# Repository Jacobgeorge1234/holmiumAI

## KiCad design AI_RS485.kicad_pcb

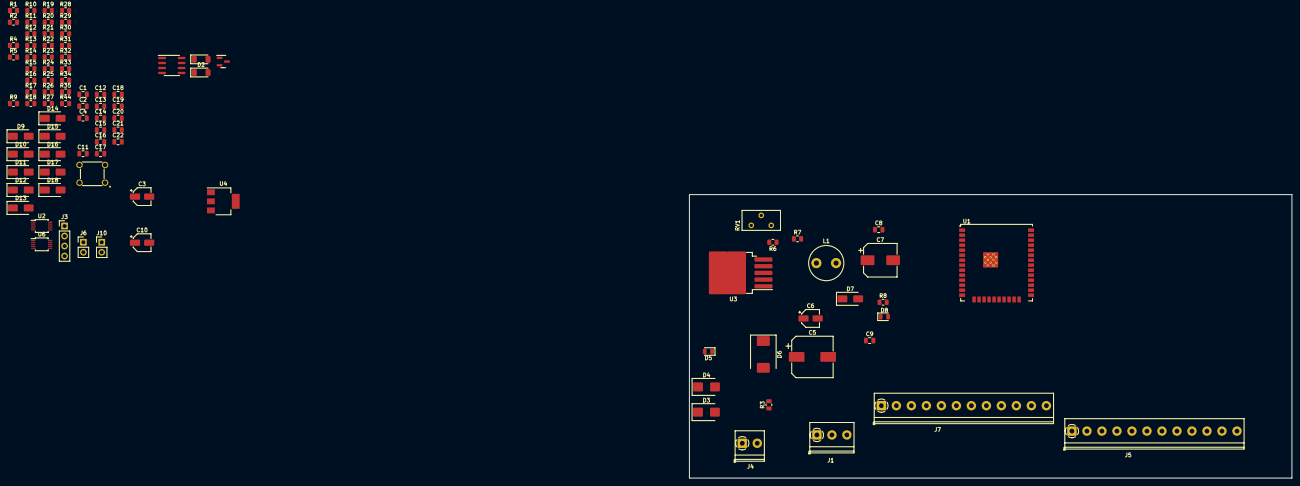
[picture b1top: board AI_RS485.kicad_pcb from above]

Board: 2 copper layers, 153.0 x 72.0 mm, 93 parts (0 on the bottom side), 55 nets, no tracks yet.

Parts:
C1: 1uF/50V; C_0805_2012Metric
C2, C12, C13, C14, C15, C16, C17, C18, C19, C20, C21, C22: 100nF/50V; C_0805_2012Metric
C3, C6, C10: 1uF; CP_Elec_4x5.4
C4, C8: 100nF; C_0805_2012Metric
C5: 100uF; CP_Elec_10x10
C7: 330uF; CP_Elec_8x10
C9, C11: 1uF; C_0805_2012Metric
D1, D2: 1N4148; D_MiniMELF
D3, D4: SMBJ36CA; D_SMB
D5, D8: LED; LED_0805_2012Metric
D6: SS54; D_SMC
D7: SS34; D_SMA
D9, D10, D11, D12, D13, D14, D15, D16, D17, D18: SMBJ6CA; D_SMA
J1: Conn_01x03; CONNECTORx3
J3: Conn_01x04_Socket; PinHeader_1x04_P2.54mm_Vertical
J4: Conn_01x02_Socket; CONNECTORx2
J5, J7: Conn_01x12_Socket; CONNECTORx12
J6: Conn_01x02_Pin; PinHeader_1x02_P2.54mm_Vertical
J10: Conn_01x02_Male; PinHeader_1x02_P2.54mm_Vertical
L1: 68uH; L_Radial_D8.7mm_P5.00mm_Fastron_07HCP
Q1: BC847; SOT-23
R1: 10k; R_0805_2012Metric
R2, R17, R18, R19, R20, R21, R22, R23: 220; R_0805_2012Metric
R3, R4, R5, R7, R8: 4K7; R_0805_2012Metric
R6, R12, R13: 1K; R_0805_2012Metric
R9, R10, R28, R29, R30, R31, R32, R33, R34, R35: 10K; R_0805_2012Metric
R11, R16, R25, R44: 0E; R_0805_2012Metric
R14, R15: 510E; R_0805_2012Metric
R24: 120E; R_0805_2012Metric
R26, R27: R; R_0805_2012Metric
RV1: 4K7; Potentiometer_Bourns_3386X_Horizontal
SW1: SW_Push; BNF_Pushbutton
U1: ESP32-WROOM-32U
U2, U6: ADS1115IDGS; TSSOP-10_3x3mm_P0.5mm
U3: LM2596S-ADJ; TO-263-5_TabPin3
U4: AMS1117-3.3; SOT-223-3_TabPin2
U5: MAX3485; SOIC-8_3.9x4.9mm_P1.27mm

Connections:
485_TX: R9.1, R12.1
+3.3V: C2.1, C3.1, C4.1, J10.1, R1.2, R10.1, R14.2, R26.1, R27.1, R28.2, R29.2, R30.2, R31.2, R32.2, R33.2, R34.2, R35.2, U1.2 (VDD), U5.8 (VCC)
+5V: C12.1, C14.1, U2.8 (VDD), U6.1 (ADDR), U6.8 (VDD)
+12V: D4.2, D5.1 (K), D6.2 (A), J4.2
ADS_DRDY_1: U1.4 (SENSOR_VP), U2.2 (ALERT/RDY)
ADS_DRDY_2: U1.5 (SENSOR_VN), U6.2 (ALERT/RDY)
AIN_0: C15.1, C19.1, R2.1, R20.1, U2.4 (AIN0)
AIN_1: C16.1, C20.1, R19.1, R23.1, U2.5 (AIN1)
AIN_2: C17.1, C21.1, R17.1, R21.1, U2.6 (AIN2)
AIN_3: C18.1, C22.1, R18.1, R22.1, U2.7 (AIN3)
BOOT: J6.1, U1.25 (IO0)
EN: C1.2, R1.1, R16.2, U1.3 (EN)
GND: C1.1, C2.2, C3.2, C4.2, C5.2, C6.2, C7.2, C8.1, C9.2, C10.2, C11.2, C12.2, C13.1, C14.2, C15.2, C16.2, C17.2, C18.2, C19.2, C20.2, C21.2, C22.2, D3.2, D7.2 (A), D8.1 (K), D9.2 (A2), D10.2 (A2), D11.2 (A2), D12.2 (A2), D13.2 (A2), D14.2 (A2), D15.2 (A2), D16.2 (A2), D17.1 (A1), D18.2 (A2), J3.1, J4.1, J5.3, J5.6, J5.9, J5.12, J6.2, J7.3, J7.6, J7.9, J7.12, R3.1, R5.2, R6.1, R11.2, R15.1, SW1.1, U1.1 (GND), U1.15 (GND), U1.38 (GND), U1.39 (GND), U2.1 (ADDR), U2.3 (GND), U3.3 (GND), U3.5 (~ON/OFF), U4.1 (GND), U5.5 (GND), U6.3 (GND)
GNDPWR: D3.1, D4.1
unnamed: C13.2, R16.1, SW1.2
unnamed: D1.2 (A), J3.2
unnamed: D2.1 (K), J3.3
unnamed: D5.2 (A), R3.2
unnamed: C5.1, C6.1, D6.1 (K), R4.1, U3.1 (VIN)
unnamed: D7.1 (K), L1.1, U3.2 (OUT)
unnamed: D8.2 (A), R8.2
unnamed: D9.1 (A1), J5.2, R2.2
unnamed: D10.1 (A1), J5.5, R19.2
unnamed: D11.1 (A1), J5.8, R17.2
unnamed: D12.1 (A1), J5.11, R18.2
unnamed: D13.1 (A1), J7.2, R20.2
unnamed: D14.1 (A1), J7.5, R23.2
unnamed: D15.1 (A1), J7.8, R21.2
unnamed: D16.1 (A1), J7.11, R22.2
unnamed: D17.2 (A2), J1.1, R25.2
unnamed: D18.1 (A1), J1.2, R44.2
unnamed: J5.1, R35.1
unnamed: J5.4, R34.1
unnamed: J5.7, R33.1
unnamed: J5.10, R32.1
unnamed: J7.1, R28.1
unnamed: J7.4, R29.1
unnamed: J7.7, R30.1
unnamed: J7.10, R31.1
unnamed: C10.1, C11.1, J10.2, U4.2 (VO)
unnamed: Q1.1 (B), R9.2
unnamed: Q1.3 (C), R10.2, U5.2 (~RE), U5.3 (DE)
unnamed: Q1.2 (E), R11.1
unnamed: R6.2, R7.1, RV1.3
unnamed: RV1.2, U3.4 (FB)
unnamed: R14.1, R24.2, R25.1, U5.6 (A)
unnamed: R15.2, R24.1, R44.1, U5.7 (B)
unnamed: R12.2, U5.4 (DI)
unnamed: R13.2, U5.1 (RO)
PWR_DET: R4.2, R5.1
RX: D2.2 (A), U1.34 (RXD0/IO3)
SCL: R27.2, U1.36 (IO22), U2.10 (SCL), U6.10 (SCL)
SDA: R26.2, U1.33 (IO21), U2.9 (SDA), U6.9 (SDA)
TX: D1.1 (K), U1.35 (TXD0/IO1)
VBAT: C7.1, C8.2, C9.1, L1.2, R7.2, R8.1, RV1.1, U4.3 (VI)
